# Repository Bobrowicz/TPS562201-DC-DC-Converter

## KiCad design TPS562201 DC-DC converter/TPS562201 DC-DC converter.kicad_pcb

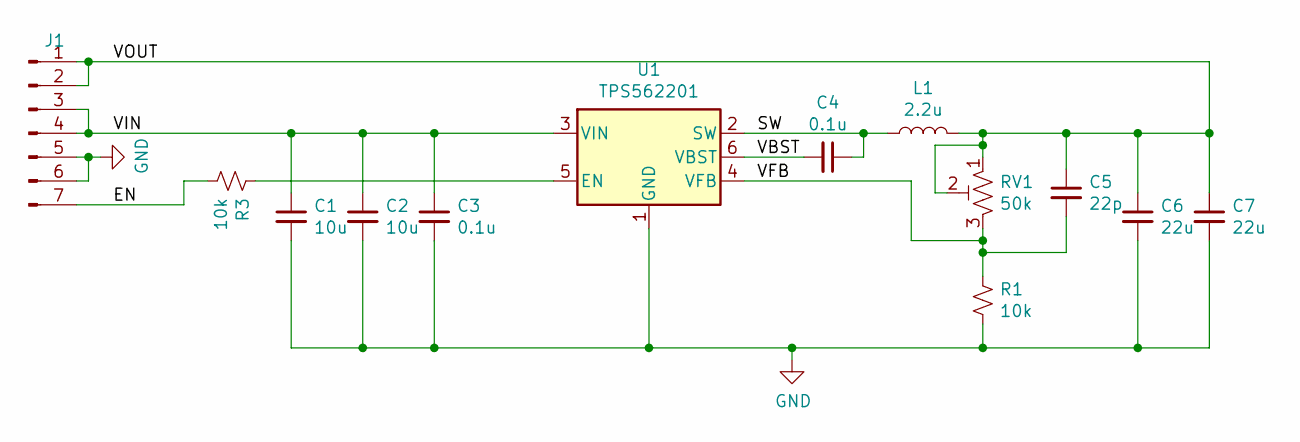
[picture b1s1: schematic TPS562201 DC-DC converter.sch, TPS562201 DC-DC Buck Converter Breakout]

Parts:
C1, C2: 10u; C_0805_HandSoldering
C3, C4: 0.1u; C_0805_HandSoldering
C5: 22p; C_0805_HandSoldering
C6, C7: 22u; C_0805_HandSoldering
J1: Conn_01x07_Male; Pin_Header_Straight_1x07_Pitch2.54mm
L1: 2.2u; Inductor_Wurth_HCI-5040
R1, R3: 10k; C_0805_HandSoldering
RV1: 50k; Potentiometer_Trimmer_Bourns_3266W
U1: TPS562201; SOT-23-6_Handsoldering

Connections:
/EN: J1.7, R3.2
/SW: C4.1, L1.1, U1.2 (SW)
/VBST: C4.2, U1.6 (VBST)
/VFB: C5.2, R1.1, RV1.3, U1.4 (VFB)
/VIN: C1.1, C2.1, C3.1, J1.3, J1.4, U1.3 (VIN)
/VOUT: C5.1, C6.1, C7.1, J1.1, J1.2, L1.2, RV1.1, RV1.2
GND: C1.2, C2.2, C3.2, C6.2, C7.2, J1.5, J1.6, R1.2, U1.1 (GND)
unnamed: R3.1, U1.5 (EN)

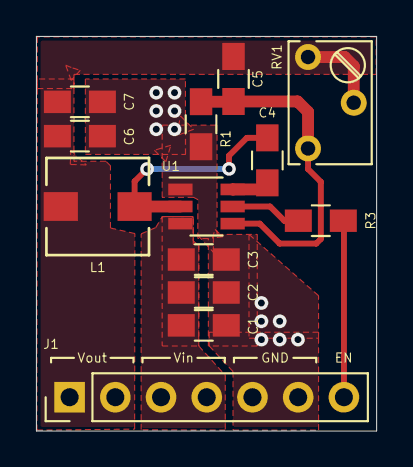
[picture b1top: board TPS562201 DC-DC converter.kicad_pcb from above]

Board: 2 copper layers, 18.9 x 21.9 mm, 13 parts (0 on the bottom side), 8 nets.

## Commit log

2021-06-11 Schematic and layout correction.
    Changed how trimmer potentiometer is connected.
